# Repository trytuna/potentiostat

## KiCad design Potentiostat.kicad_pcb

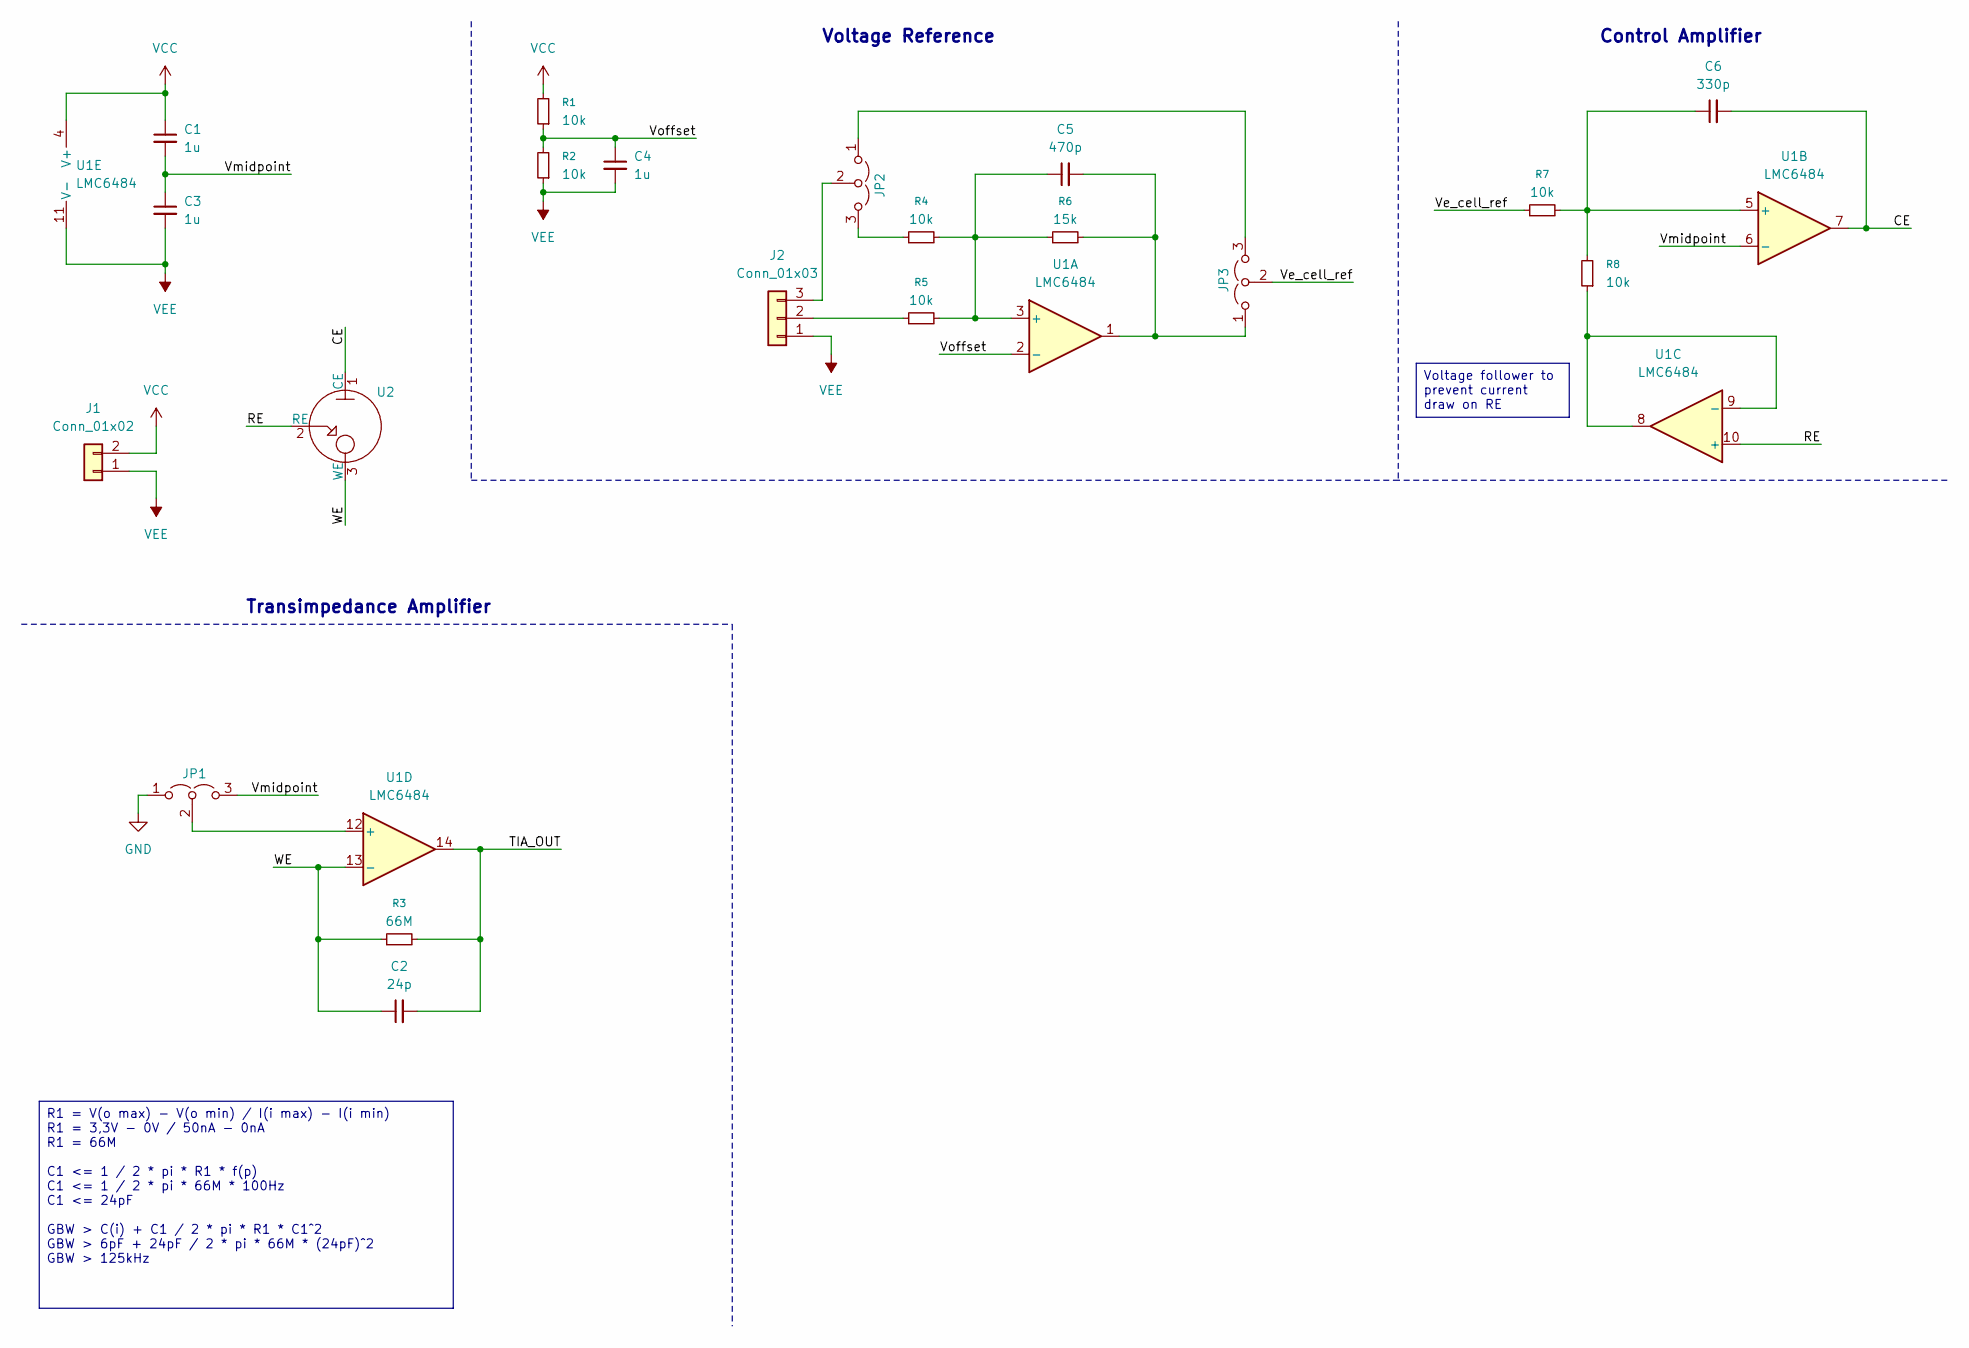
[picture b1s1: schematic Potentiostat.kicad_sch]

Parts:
C1, C3, C4: 1u; C_0603_1608Metric_Pad1.08x0.95mm_HandSolder
C2: 24p; C_0603_1608Metric_Pad1.08x0.95mm_HandSolder
C5: 470p; C_0603_1608Metric_Pad1.08x0.95mm_HandSolder
C6: 330p; C_0603_1608Metric_Pad1.08x0.95mm_HandSolder
J1: Conn_01x02; PinHeader_1x02_P2.54mm_Vertical
J2: Conn_01x03; PinHeader_1x03_P2.54mm_Vertical
JP1, JP2, JP3: Jumper_3_Open; PinHeader_1x03_P2.54mm_Vertical
R1, R2, R4, R5, R7, R8: 10k; R_0603_1608Metric_Pad0.98x0.95mm_HandSolder
R3: 66M; R_0603_1608Metric_Pad0.98x0.95mm_HandSolder
R6: 15k; R_0603_1608Metric_Pad0.98x0.95mm_HandSolder
U1: LMC6484; SOIC-14_3.9x8.7mm_P1.27mm
U2: PinHeader_1x03_P2.54mm_Vertical

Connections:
/CE: C6.2, U1.7, U2.1 (CE); also elsewhere on the board
/RE: U1.10 (+), U2.2 (RE); also elsewhere on the board
/TIA_OUT: C2.2, R3.2, U1.14
/Ve_cell_ref: JP3.2 (C), R7.1
/Vmidpoint: C1.2, C3.1, JP1.3 (B), U1.6 (-)
/Voffset: C4.1, R1.1, R2.2, U1.2 (-)
/WE: C2.1, R3.1, U1.13 (-), U2.3 (WE); also elsewhere on the board
GND: JP1.1 (A)
unnamed: J2.2, R5.1
unnamed: J2.3, JP2.2 (C)
unnamed: JP1.2 (C), U1.12 (+)
unnamed: JP2.1 (A), JP3.3 (B)
unnamed: JP2.3 (B), R4.1
unnamed: C5.2, JP3.1 (A), R6.2, U1.1
unnamed: C5.1, R4.2, R5.2, R6.1, U1.3 (+)
unnamed: C6.1, R7.2, R8.2, U1.5 (+)
unnamed: R8.1, U1.8, U1.9 (-)
VCC: C1.1, J1.2, R1.2, U1.4 (V+)
VEE: C3.2, C4.2, J1.1, J2.1, R2.1, U1.11 (V-)

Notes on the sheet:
Control Amplifier
Transimpedance Amplifier
Voltage Reference
R1 = V(o max) - V(o min) / I(i max) - I(i min) R1 = 3,3V - 0V / 50nA - 0nA R1 = 66M C1 <= 1 / 2 * pi * R1 * f(p) C1 <= 1 / 2 * pi * 66M * 100Hz C1 <= 24pF GBW > C(i) + C1 / 2 * pi * R1 * C1^2 GBW > 6pF + 24pF / 2 * pi * 66M * (24pF)^2 GBW > 125kHz
Voltage follower to prevent current draw on RE

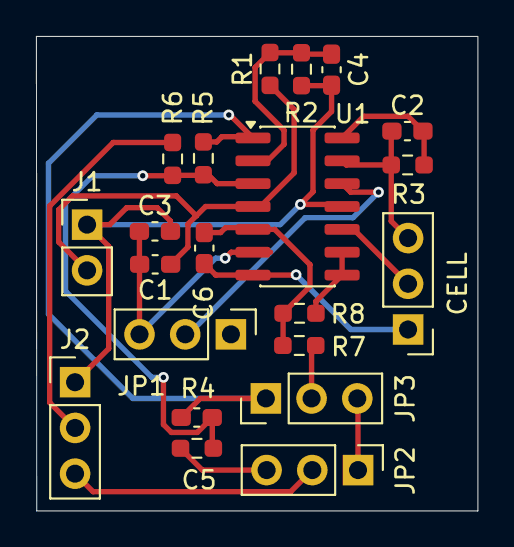
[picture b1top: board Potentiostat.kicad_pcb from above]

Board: 2 copper layers, 24.5 x 26.4 mm, 21 parts (0 on the bottom side), 18 nets.

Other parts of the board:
CELL: PinHeader_1x03_P2.54mm_Vertical

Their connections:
/CE: CELL.1 (CE); also elsewhere on the board
/RE: CELL.2 (RE); also elsewhere on the board
/WE: CELL.3 (WE); also elsewhere on the board

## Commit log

2026-01-08 basic potentiostat design
2026-01-13 Add electrochemical cell with simulation
2026-01-13 Add alternative pwl for V2 as comment
